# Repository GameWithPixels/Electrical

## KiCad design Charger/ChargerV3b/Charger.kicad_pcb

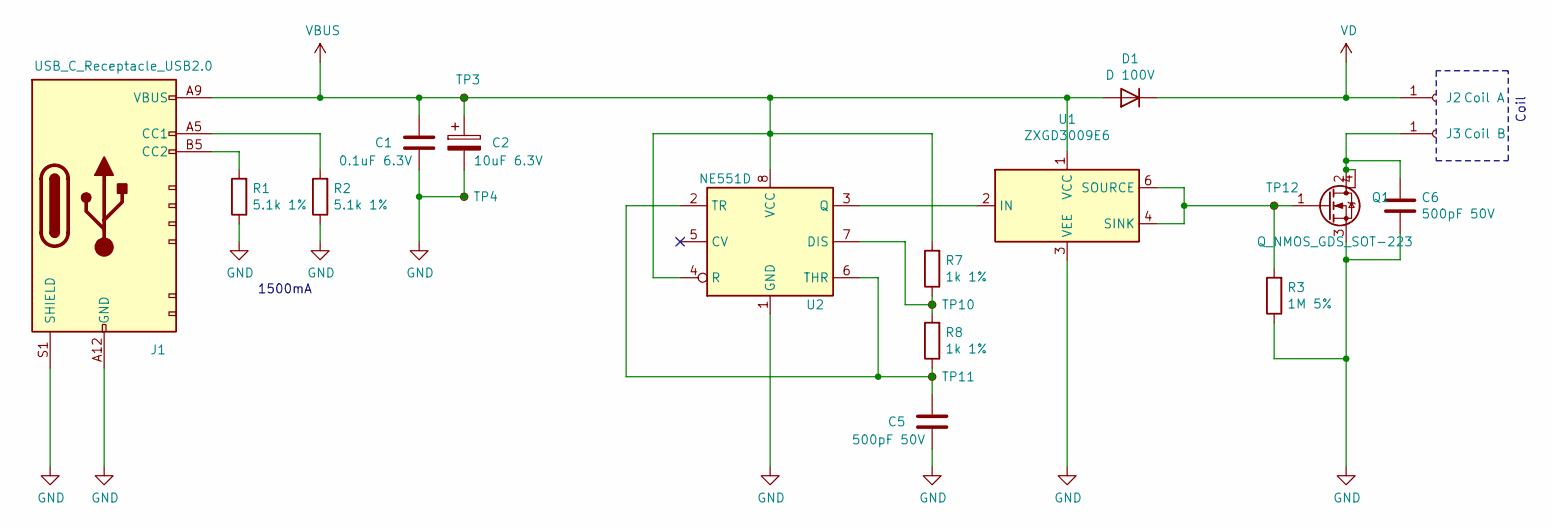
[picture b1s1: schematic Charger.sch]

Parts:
C1: 0.1uF 6.3V; C_0603_1608Metric; Part Number TCC0603X7R104K500CT; LCSC Part Number C282519
C2: 10uF 6.3V; C_0603_1608Metric; Part Number CL10A106MP8NNNC; LCSC Part Number C85713
C5, C6: 500pF 50V; C_0805_2012Metric; Part Number CC0805KRX7R0BB471; LCSC Part Number C107138
D1: D 100V; D_SOD-123F; Part Number DSS210; LCSC Part Number C511868
J1: USB_C_Receptacle_USB2.0; USB-C-SMD_10P-P1.00-L6.8-W8.9; Part Number TYPE-C-31-M-17; LCSC Part Number C283540
J2: Coil A; TestPoint_THTPad_D2.0mm_Drill1.0mm
J3: Coil B; TestPoint_THTPad_D2.0mm_Drill1.0mm
Q1: Q_NMOS_GDS_SOT-223; SOT-223; Part Number HSL0004; LCSC Part Number C508454
R1, R2: 5.1k 1%; R_0603_1608Metric; Part Number WR06X5101FTL; LCSC Part Number C113390
R3: 1M 5%; R_0603_1608Metric; Part Number 0603WAJ0105T5E; LCSC Part Number C26098
R7, R8: 1k 1%; R_0603_1608Metric; Part Number 0603WAF1001T5E; LCSC Part Number C21190
TP3, TP4, TP10, TP11, TP12: TestPoint_Small; TestPoint_Pad_1.0x1.0mm
U1: ZXGD3009E6; SOT-363_SC-70-6; Part Number ZXGD3009DYTA; LCSC Part Number C441818
U2: NE551D; SOP-8_3.9x4.9mm_P1.27mm; Part Number XL551; LCSC Part Number C707074

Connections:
GND: C1.2, C2.2, C5.2, C6.2, J1.A12 (GND), J1.B12 (GND), J1.S1 (SHIELD), Q1.3 (S), R1.1, R2.1, R3.1, TP4.1, U1.3 (VEE), U2.1 (GND)
unnamed: C5.1, R8.1, TP11.1, U2.2 (TR), U2.6 (THR)
unnamed: C6.1, J3.1, Q1.2 (D), Q1.4
unnamed: J1.A5 (CC1), R2.2
unnamed: J1.B5 (CC2), R1.2
unnamed: Q1.1 (G), R3.2, TP12.1, U1.4 (SINK), U1.6 (SOURCE)
unnamed: R7.1, R8.2, TP10.1, U2.7 (DIS)
unnamed: U1.2 (IN), U2.3 (Q)
VBUS: C1.1, C2.1, D1.2 (A), J1.A9 (VBUS), J1.B9 (VBUS), R7.2, TP3.1, U1.1 (VCC), U2.4 (R), U2.8 (VCC)
VD: D1.1 (K), J2.1

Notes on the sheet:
1500mA
Coil

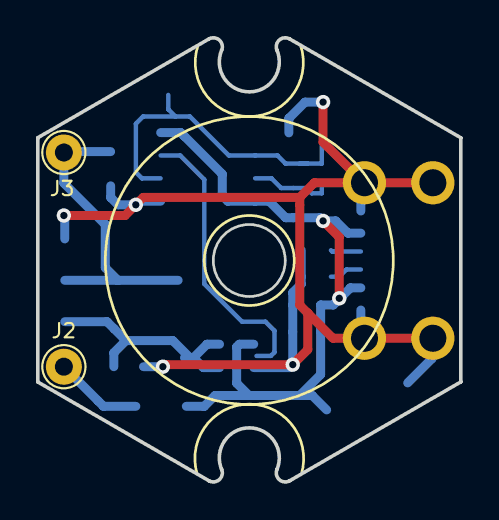
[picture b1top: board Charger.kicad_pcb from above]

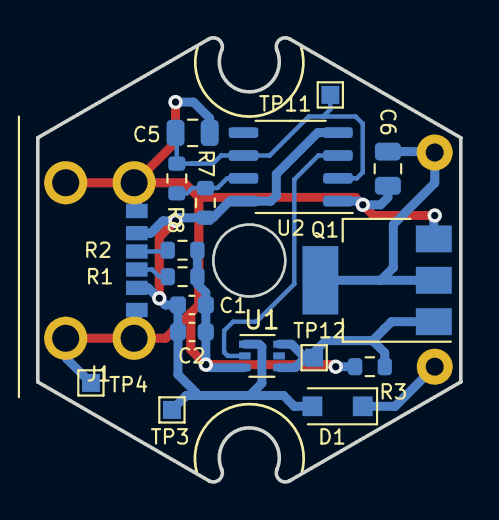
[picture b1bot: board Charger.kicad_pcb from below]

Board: 2 copper layers, 23.5 x 24.7 mm, 20 parts (18 on the bottom side), 10 nets.

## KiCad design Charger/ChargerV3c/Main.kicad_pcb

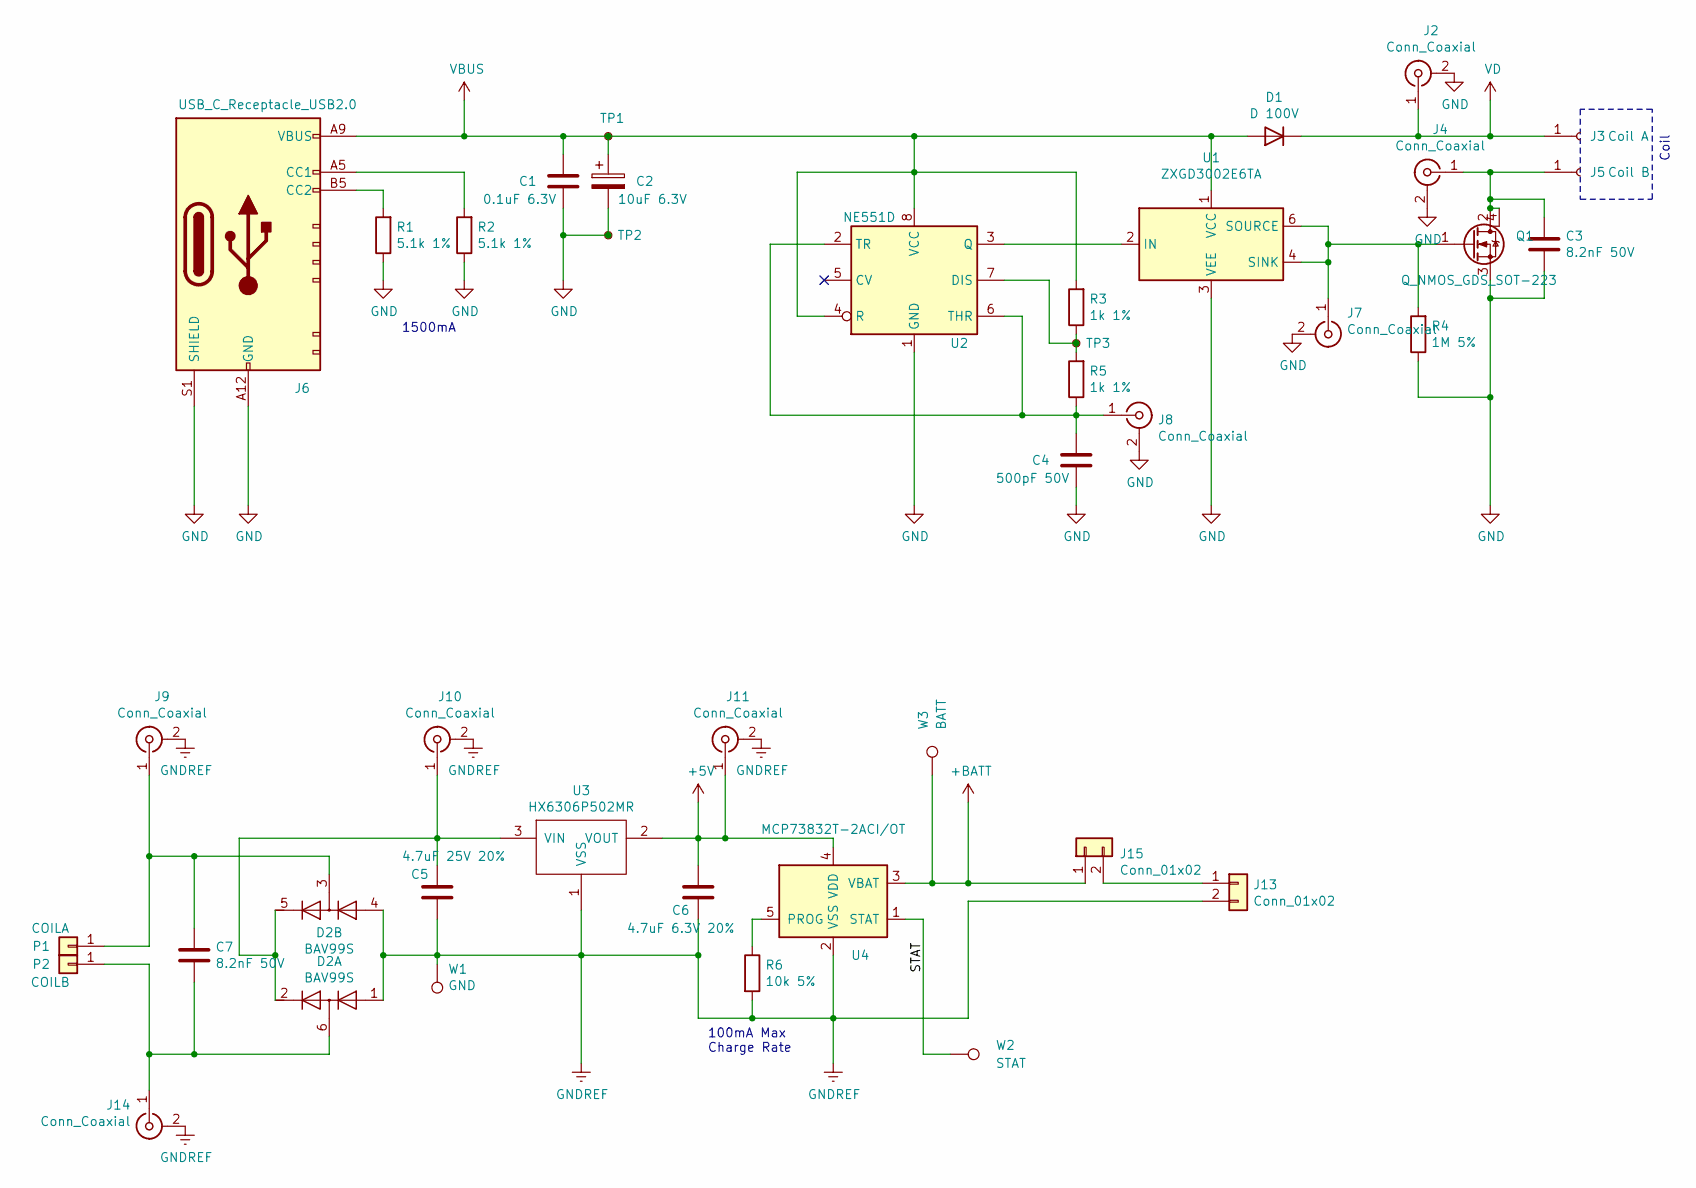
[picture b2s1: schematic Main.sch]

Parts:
C1: 0.1uF 6.3V; C_0603_1608Metric; Part Number TCC0603X7R104K500CT; LCSC Part Number C282519
C2: 10uF 6.3V; C_0603_1608Metric; Part Number CL10A106MP8NNNC; LCSC Part Number C85713
C3, C7: 8.2nF 50V; C_0805_2012Metric; Part Number CC0805KRX7R0BB471; LCSC Part Number C107138
C4: 500pF 50V; C_0805_2012Metric; Part Number CC0805KRX7R0BB471; LCSC Part Number C107138
C5: 4.7uF 25V 20%; C_0805_2012Metric; Part Number CL21A475KAQNNNE; LCSC Part Number C1779
C6: 4.7uF 6.3V 20%; C_0603_1608Metric; Manufacturer Part Number CL10A475MQ8NNNC; LCSC Part Number C154959
D1: D 100V; D_SOD-123F; Part Number DSS210; LCSC Part Number C511868
D2: BAV99S; SOT-363_SC-70-6; Part Number BAV99SH6327XTSA1; LCSC Part Number C68987
J2, J4, J7, J8, J9, J10, J11, J14: Conn_Coaxial; U.FL-R-SMT-1(80); Part Number U.FL-R-SMT-1(80); LCSC Part Number C88374
J3: Coil A; TestPoint_THTPad_D2.0mm_Drill1.0mm
J5: Coil B; TestPoint_THTPad_D2.0mm_Drill1.0mm
J6: USB_C_Receptacle_USB2.0; USB-C-SMD_10P-P1.00-L6.8-W8.9; Part Number TYPE-C-31-M-17; LCSC Part Number C283540
J13: Conn_01x02; Hongjie 10100 Connector
J15: Conn_01x02; PinHeader_1x02_P2.54mm_Vertical
P1: COILA; TestPoint_THTPad_D1.5mm_Drill0.7mm
P2: COILB; TestPoint_THTPad_D1.5mm_Drill0.7mm
Q1: Q_NMOS_GDS_SOT-223; SOT-223; Part Number HSL0004; LCSC Part Number C508454
R1, R2: 5.1k 1%; R_0603_1608Metric; Part Number WR06X5101FTL; LCSC Part Number C113390
R3, R5: 1k 1%; R_0603_1608Metric; Part Number 0603WAF1001T5E; LCSC Part Number C21190
R4: 1M 5%; R_0603_1608Metric; Part Number 0603WAJ0105T5E; LCSC Part Number C26098
R6: 10k 5%; R_0402_1005Metric; Part Number RC0402FR-0710KL; LCSC Part Number C60490
TP1, TP2, TP3: TestPoint_Small; TestPoint_Pad_1.0x1.0mm
U1: ZXGD3002E6TA; SOT-23-6; Part Number ZXGD3002E6TA; LCSC Part Number C156276
U2: NE551D; SOP-8_3.9x4.9mm_P1.27mm; Part Number XL551; LCSC Part Number C707074
U3: HX6306P502MR; SOT-23; Part Number HX6306P502MR; LCSC Part Number C296209
U4: MCP73832T-2ACI/OT; SOT-23-5; Part Number MCP73832T-2ACI/OT; LCSC Part Number C38066
W1: GND; TestPoint_Pad_1.0x1.0mm
W2: STAT; TestPoint_Pad_1.0x1.0mm
W3: BATT; TestPoint_Pad_1.0x1.0mm

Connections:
+5V: C6.1, J11.1 (In), U3.2 (VOUT), U4.4 (VDD)
+BATT: J15.1, U4.3 (VBAT), W3.1
/STAT: U4.1 (STAT), W2.1
GND: C1.2, C2.2, C3.2, C4.2, J2.2 (Ext), J4.2 (Ext), J6.A12 (GND), J6.B12 (GND), J6.S1 (SHIELD), J7.2 (Ext), J8.2 (Ext), Q1.3 (S), R1.1, R2.1, R4.1, TP2.1, U1.3 (VEE), U2.1 (GND)
GNDREF: C5.2, C6.2, D2.1 (A1), D2.4 (A3), J9.2 (Ext), J10.2 (Ext), J11.2 (Ext), J13.2, J14.2 (Ext), R6.2, U3.1 (VSS), U4.2 (VSS), W1.1
unnamed: C3.1, J4.1 (In), J5.1, Q1.2 (D), Q1.4
unnamed: C4.1, J8.1 (In), R5.1, U2.2 (TR), U2.6 (THR)
unnamed: C5.1, D2.2 (K2), D2.5 (K4), J10.1 (In), U3.3 (VIN)
unnamed: C7.1, D2.3 (K1A2), J9.1 (In), P1.1
unnamed: C7.2, D2.6 (K3A4), J14.1 (In), P2.1
unnamed: J6.A5 (CC1), R2.2
unnamed: J6.B5 (CC2), R1.2
unnamed: J7.1 (In), Q1.1 (G), R4.2, U1.4 (SINK), U1.6 (SOURCE)
unnamed: J13.1, J15.2
unnamed: R3.1, R5.2, TP3.1, U2.7 (DIS)
unnamed: R6.1, U4.5 (PROG)
unnamed: U1.2 (IN), U2.3 (Q)
VBUS: C1.1, C2.1, D1.2 (A), J6.A9 (VBUS), J6.B9 (VBUS), R3.2, TP1.1, U1.1 (VCC), U2.4 (R), U2.8 (VCC)
VD: D1.1 (K), J2.1 (In), J3.1

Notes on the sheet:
100mA Max Charge Rate
1500mA
Coil

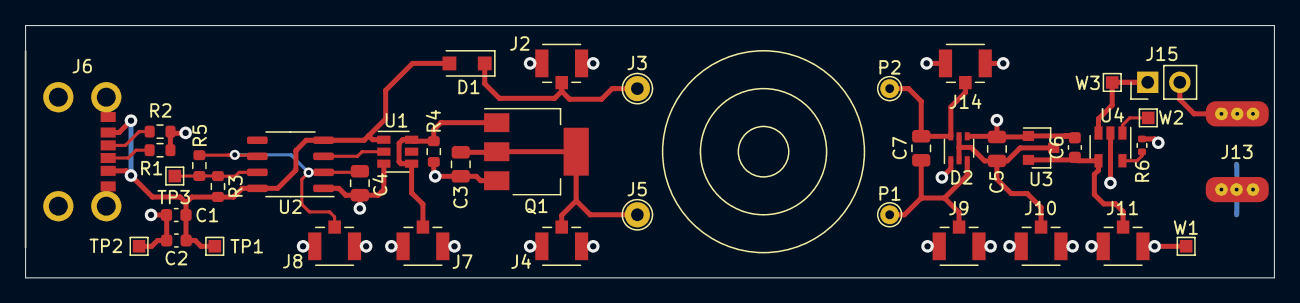
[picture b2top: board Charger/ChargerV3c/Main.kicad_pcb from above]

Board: 2 copper layers, 99.0 x 20.0 mm, 41 parts (0 on the bottom side), 19 nets.

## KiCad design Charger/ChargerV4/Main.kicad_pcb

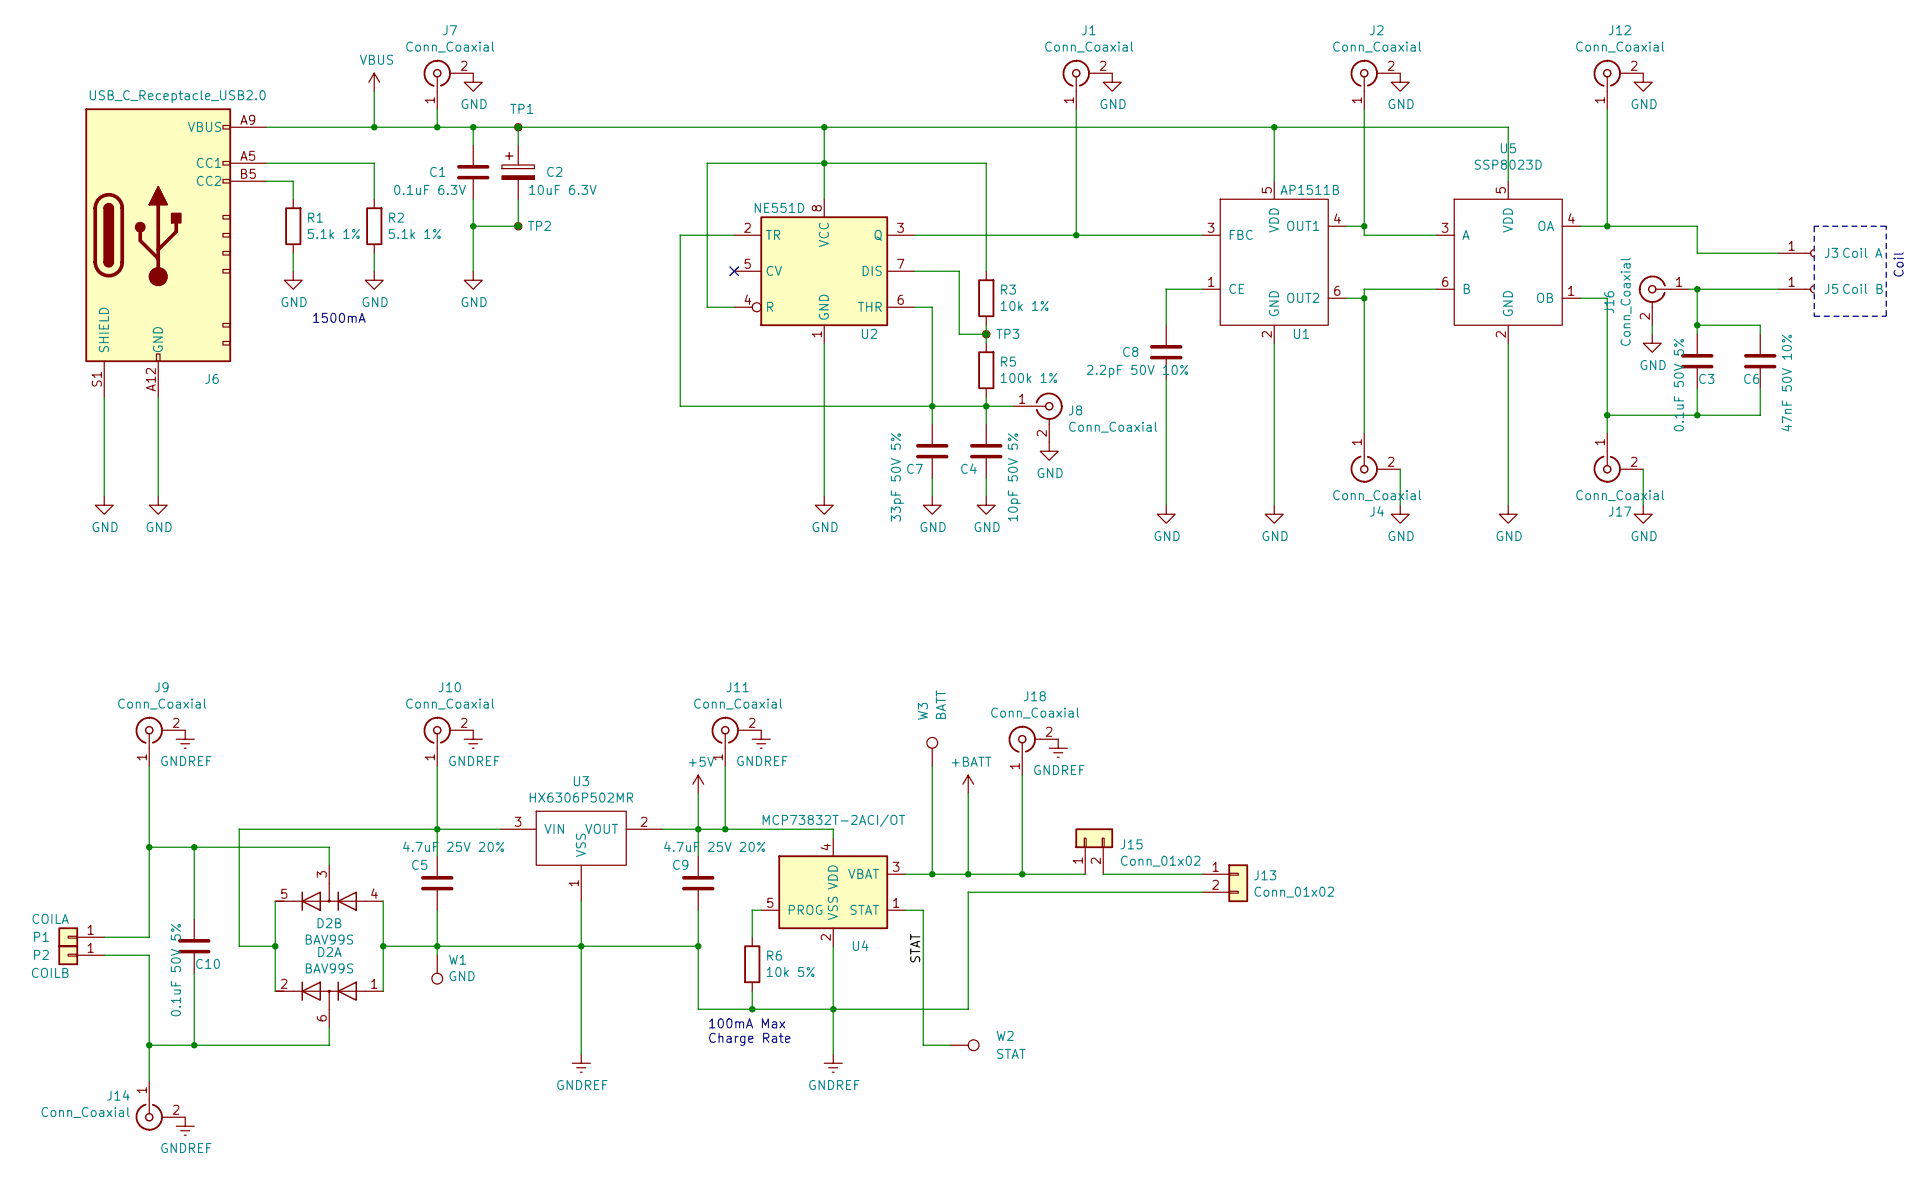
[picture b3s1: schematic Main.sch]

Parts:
C1: 0.1uF 6.3V; C_0603_1608Metric; Part Number TCC0603X7R104K500CT; LCSC Part Number C282519
C2: 10uF 6.3V; C_0603_1608Metric; Part Number CL10A106MP8NNNC; LCSC Part Number C85713
C3, C10: 0.1uF 50V 5%; C_0805_2012Metric; Part Number CL21B104JBCNNNC; LCSC Part Number C62912
C4: 10pF 50V 5%; C_0603_1608Metric; Part Number CL10C100JB8NNNC; LCSC Part Number C1634
C5, C9: 4.7uF 25V 20%; C_0805_2012Metric; Part Number CL21A475KAQNNNE; LCSC Part Number C1779
C6: 47nF 50V 10%; C_0603_1608Metric; Part Number CL10B104JB8NNNCCopy; LCSC Part Number C24452
C7: 33pF 50V 5%; C_0603_1608Metric; Part Number CL10C330JB8NNNC; LCSC Part Number C1663
C8: 2.2pF 50V 10%; C_0603_1608Metric; Part Number CL10C2R2CB8NNNC; LCSC Part Number C84711
D2: BAV99S; SOT-363_SC-70-6; Part Number BAV99SH6327XTSA1; LCSC Part Number C68987
J1, J2, J4, J7, J8, J9, J10, J11, J12, J14, J16, J17, J18: Conn_Coaxial; U.FL-R-SMT-1(80); Part Number U.FL-R-SMT-1(80); LCSC Part Number C88374
J3: Coil A; TestPoint_THTPad_D2.0mm_Drill1.0mm
J5: Coil B; TestPoint_THTPad_D2.0mm_Drill1.0mm
J6: USB_C_Receptacle_USB2.0; USB-C-SMD_10P-P1.00-L6.8-W8.9; Part Number TYPE-C-31-M-17; LCSC Part Number C283540
J13: Conn_01x02; Hongjie 10100 Connector
J15: Conn_01x02; PinHeader_1x02_P2.54mm_Vertical
P1: COILA; TestPoint_THTPad_D1.5mm_Drill0.7mm
P2: COILB; TestPoint_THTPad_D1.5mm_Drill0.7mm
R1, R2: 5.1k 1%; R_0603_1608Metric; Part Number WR06X5101FTL; LCSC Part Number C113390
R3: 10k 1%; R_0603_1608Metric; LCSC Part Number C25804
R5: 100k 1%; R_0603_1608Metric; LCSC Part Number C25803
R6: 10k 5%; R_0402_1005Metric; Part Number RC0402FR-0710KL; LCSC Part Number C60490
TP1, TP2, TP3: TestPoint_Small; TestPoint_Pad_1.0x1.0mm
U1: AP1511B; SOT-26; LCSC Part Number C347457
U2: NE551D; SOP-8_3.9x4.9mm_P1.27mm; Part Number XL551; LCSC Part Number C707074
U3: HX6306P502MR; SOT-23; Part Number HX6306P502MR; LCSC Part Number C296209
U4: MCP73832T-2ACI/OT; SOT-23-5; Part Number MCP73832T-2ACI/OT; LCSC Part Number C38066
U5: SSP8023D; TSOT-23-6; LCSC Part Number C410985
W1: GND; TestPoint_Pad_1.0x1.0mm
W2: STAT; TestPoint_Pad_1.0x1.0mm
W3: BATT; TestPoint_Pad_1.0x1.0mm

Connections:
+5V: C9.1, J11.1 (In), U3.2 (VOUT), U4.4 (VDD)
+BATT: J15.1, J18.1 (In), U4.3 (VBAT), W3.1
/STAT: U4.1 (STAT), W2.1
GND: C1.2, C2.2, C4.2, C7.2, C8.2, J1.2 (Ext), J2.2 (Ext), J4.2 (Ext), J6.A12 (GND), J6.B12 (GND), J6.S1 (SHIELD), J7.2 (Ext), J8.2 (Ext), J12.2 (Ext), J16.2 (Ext), J17.2 (Ext), R1.1, R2.1, TP2.1, U1.2 (GND), U2.1 (GND), U5.2 (GND)
GNDREF: C5.2, C9.2, D2.1 (A1), D2.4 (A3), J9.2 (Ext), J10.2 (Ext), J11.2 (Ext), J13.2, J14.2 (Ext), J18.2 (Ext), R6.2, U3.1 (VSS), U4.2 (VSS), W1.1
unnamed: C3.1, C6.1, J5.1, J16.1 (In)
unnamed: C3.2, C6.2, J17.1 (In), U5.1 (OB)
unnamed: C4.1, C7.1, J8.1 (In), R5.1, U2.2 (TR), U2.6 (THR)
unnamed: C5.1, D2.2 (K2), D2.5 (K4), J10.1 (In), U3.3 (VIN)
unnamed: C8.1, U1.1 (CE)
unnamed: C10.1, D2.3 (K1A2), J9.1 (In), P1.1
unnamed: C10.2, D2.6 (K3A4), J14.1 (In), P2.1
unnamed: J1.1 (In), U1.3 (FBC), U2.3 (Q)
unnamed: J2.1 (In), U1.4 (OUT1), U5.3 (A)
unnamed: J4.1 (In), U1.6 (OUT2), U5.6 (B)
unnamed: J6.A5 (CC1), R2.2
unnamed: J6.B5 (CC2), R1.2
unnamed: J3.1, J12.1 (In), U5.4 (OA)
unnamed: J13.1, J15.2
unnamed: R3.1, R5.2, TP3.1, U2.7 (DIS)
unnamed: R6.1, U4.5 (PROG)
VBUS: C1.1, C2.1, J6.A9 (VBUS), J6.B9 (VBUS), J7.1 (In), R3.2, TP1.1, U1.5 (VDD), U2.4 (R), U2.8 (VCC), U5.5 (VDD)

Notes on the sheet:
100mA Max Charge Rate
1500mA
Coil

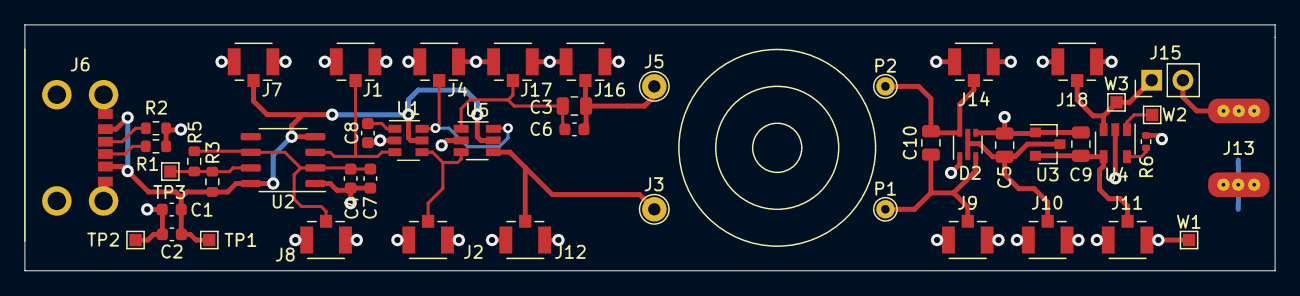
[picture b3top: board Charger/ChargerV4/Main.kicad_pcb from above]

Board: 2 copper layers, 101.7 x 20.0 mm, 47 parts (0 on the bottom side), 22 nets.

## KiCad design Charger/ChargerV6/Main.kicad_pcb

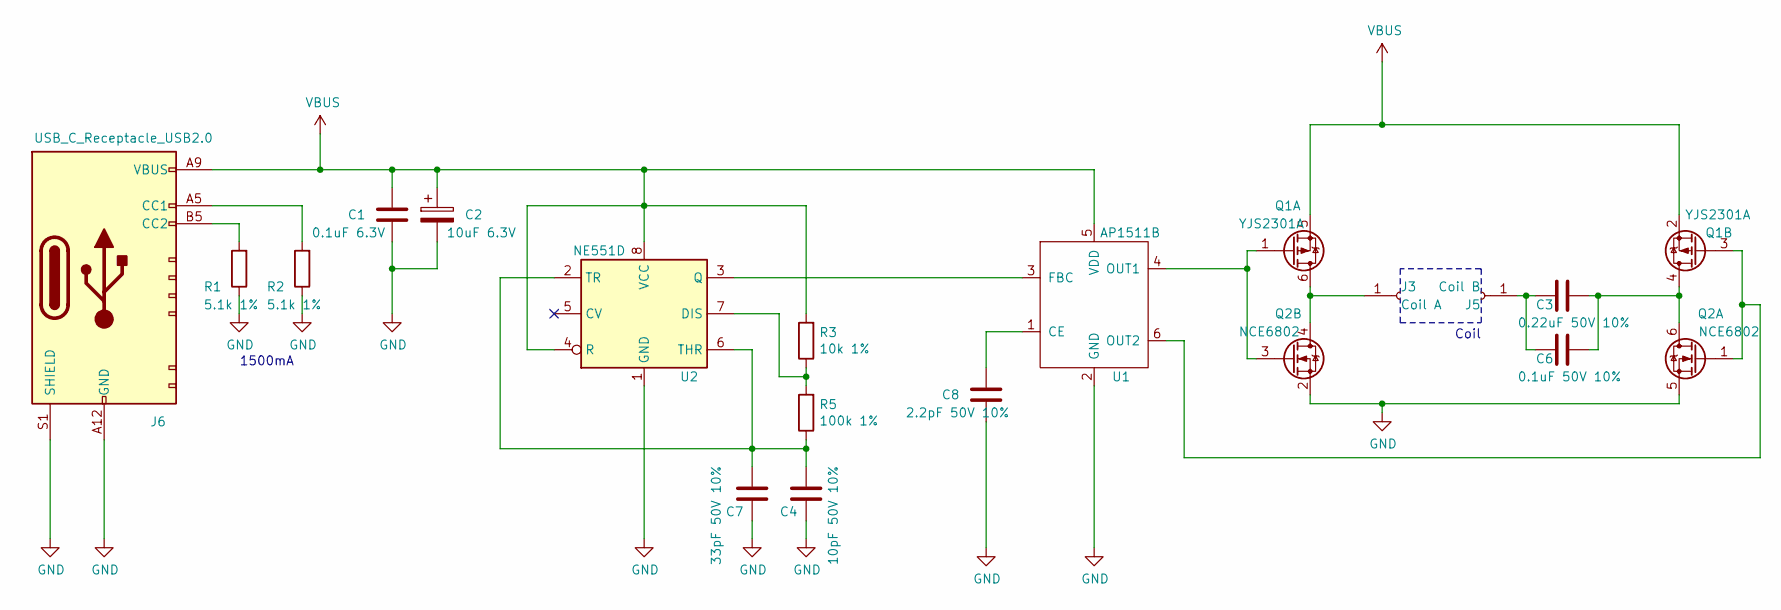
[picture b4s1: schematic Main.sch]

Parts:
C1: 0.1uF 6.3V; C_0603_1608Metric; Part Number TCC0603X7R104K500CT; LCSC Part Number C282519
C2: 10uF 6.3V; C_0603_1608Metric; Part Number CL10A106MP8NNNC; LCSC Part Number C85713
C3: 0.22uF 50V 10%; C_0805_2012Metric; Part Number CL21B224KBFNNNE; LCSC Part Number C5378
C4: 10pF 50V 10%; C_0603_1608Metric; Part Number CL10C100JB8NNNC; LCSC Part Number C1634
C6: 0.1uF 50V 10%; C_0805_2012Metric; Part Number CL21B104JBCNNNC; LCSC Part Number C62912
C7: 33pF 50V 10%; C_0603_1608Metric; Part Number CL10C330JB8NNNC; LCSC Part Number C1663
C8: 2.2pF 50V 10%; C_0603_1608Metric; Part Number CL10C2R2CB8NNNC; LCSC Part Number C84711
J3: Coil A; TestPoint_THTPad_D2.0mm_Drill1.0mm
J5: Coil B; TestPoint_THTPad_D2.0mm_Drill1.0mm
J6: USB_C_Receptacle_USB2.0; USB-C-SMD_10P-P1.00-L6.8-W8.9; Part Number TYPE-C-31-M-17; LCSC Part Number C283540
Q1: YJS2301A; SOT-23-6; Part Number YJS2301A; LCSC Part Number C699284
Q2: NCE6802; SOT-23-6; Part Number NCE6802; LCSC Part Number C502874
R1, R2: 5.1k 1%; R_0603_1608Metric; LCSC Part Number C23186
R3: 10k 1%; R_0603_1608Metric; LCSC Part Number C25804
R5: 100k 1%; R_0603_1608Metric; LCSC Part Number C25803
U1: AP1511B; SOT-26; LCSC Part Number C347457
U2: NE551D; SOP-8_3.9x4.9mm_P1.27mm; Part Number XL551; LCSC Part Number C707074

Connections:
GND: C1.2, C2.2, C4.2, C7.2, C8.2, J6.A12 (GND), J6.B12 (GND), J6.S1 (SHIELD), Q2.2 (S), Q2.5 (S), R1.1, R2.1, U1.2 (GND), U2.1 (GND)
unnamed: C3.1, C6.1, Q1.4 (D), Q2.6 (D)
unnamed: C3.2, C6.2, J5.1
unnamed: C4.1, C7.1, R5.1, U2.2 (TR), U2.6 (THR)
unnamed: C8.1, U1.1 (CE)
unnamed: J3.1, Q1.6 (D), Q2.4 (D)
unnamed: J6.A5 (CC1), R2.2
unnamed: J6.B5 (CC2), R1.2
unnamed: Q1.1 (G), Q2.3 (G), U1.4 (OUT1)
unnamed: Q1.3 (G), Q2.1 (G), U1.6 (OUT2)
unnamed: R3.1, R5.2, U2.7 (DIS)
unnamed: U1.3 (FBC), U2.3 (Q)
VBUS: C1.1, C2.1, J6.A9 (VBUS), J6.B9 (VBUS), Q1.2 (S), Q1.5 (S), R3.2, U1.5 (VDD), U2.4 (R), U2.8 (VCC)

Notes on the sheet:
1500mA
Coil

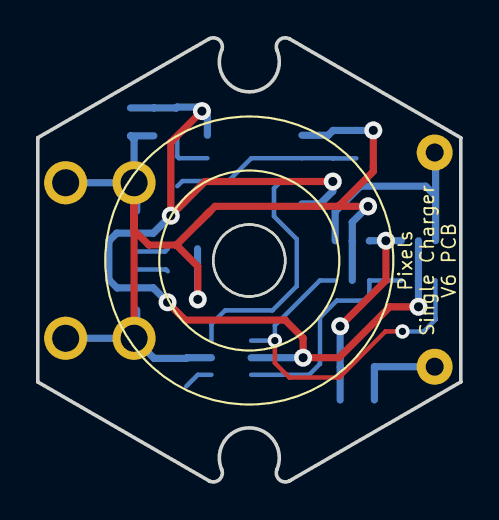
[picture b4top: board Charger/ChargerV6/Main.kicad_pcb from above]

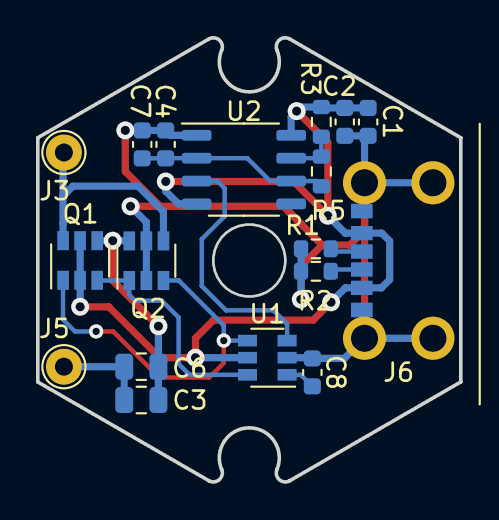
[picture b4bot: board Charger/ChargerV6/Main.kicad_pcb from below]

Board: 2 copper layers, 23.5 x 24.7 mm, 18 parts (18 on the bottom side), 13 nets.
